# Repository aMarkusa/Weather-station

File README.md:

# BLE Weather Station

The BLE Weather Station is a project I started in late 2022 as a way to get practical experience with developing low-power IoT solutions.

## Working principle
The weather station consists of two main components: a central device serving as the station, and a peripheral device serving as a temperature node.

### Peripheral device
   
The peripheral device consists of a Renesas DA14531 BLE module together with a STS40 temperature sensor. The peripheral device performs a temperature reading every 10min, and includes this reading in its advertisement data. The BLE module is set to advertise with an interval of 1s.  
The peripheral is powered with a CR2450 cell-battery. In order to minimize current consumption, non-connectable advertisements are used together with extended sleep which is entered between advertisement. With this configuration, estimations done with a power analyzer results in a battery life of ~4 years. 

### Central device
   
The main components of the central device is a Renesas DA14531 BLE module, BME680 environmental sensor, and a 4.2" E-Paper display. The central device spends most of its time in deep sleep, but wakes up every 30min to performs its task. After waking up, the central device starts scanning for the peripheral device. If the peripheral device is detected, the central reads the peripherals temperature from the advertisement data. If the peripheral cant be detected within 15s, the temperature value is set to 255. After the peripheral temperature is set, the central device performs a reading from the BME680 sensor (temperature, humidity, air-pressure, gas-resistance). So, at this point, the central has acquired 5 data values:

&nbsp;&nbsp;&nbsp;&nbsp;1. Peripheral temperature  
&nbsp;&nbsp;&nbsp;&nbsp;2. Central temperature  
&nbsp;&nbsp;&nbsp;&nbsp;3. Central humidity  
&nbsp;&nbsp;&nbsp;&nbsp;4. Central air-pressure  
&nbsp;&nbsp;&nbsp;&nbsp;5. Central gas resistance 

These values are then displayed on the E-Paper display, after which the central goes back to sleep.

## Current status
The project has reached the point where it is functioning as intended, but still has some unfinished tasks:

* Designing and 3D-printing enclosures for both the peripheral and the central.
* Calibrating the BME680's gas resistance reading and converting it into an air quality grade.
* Performing current consumption measurements on the central.

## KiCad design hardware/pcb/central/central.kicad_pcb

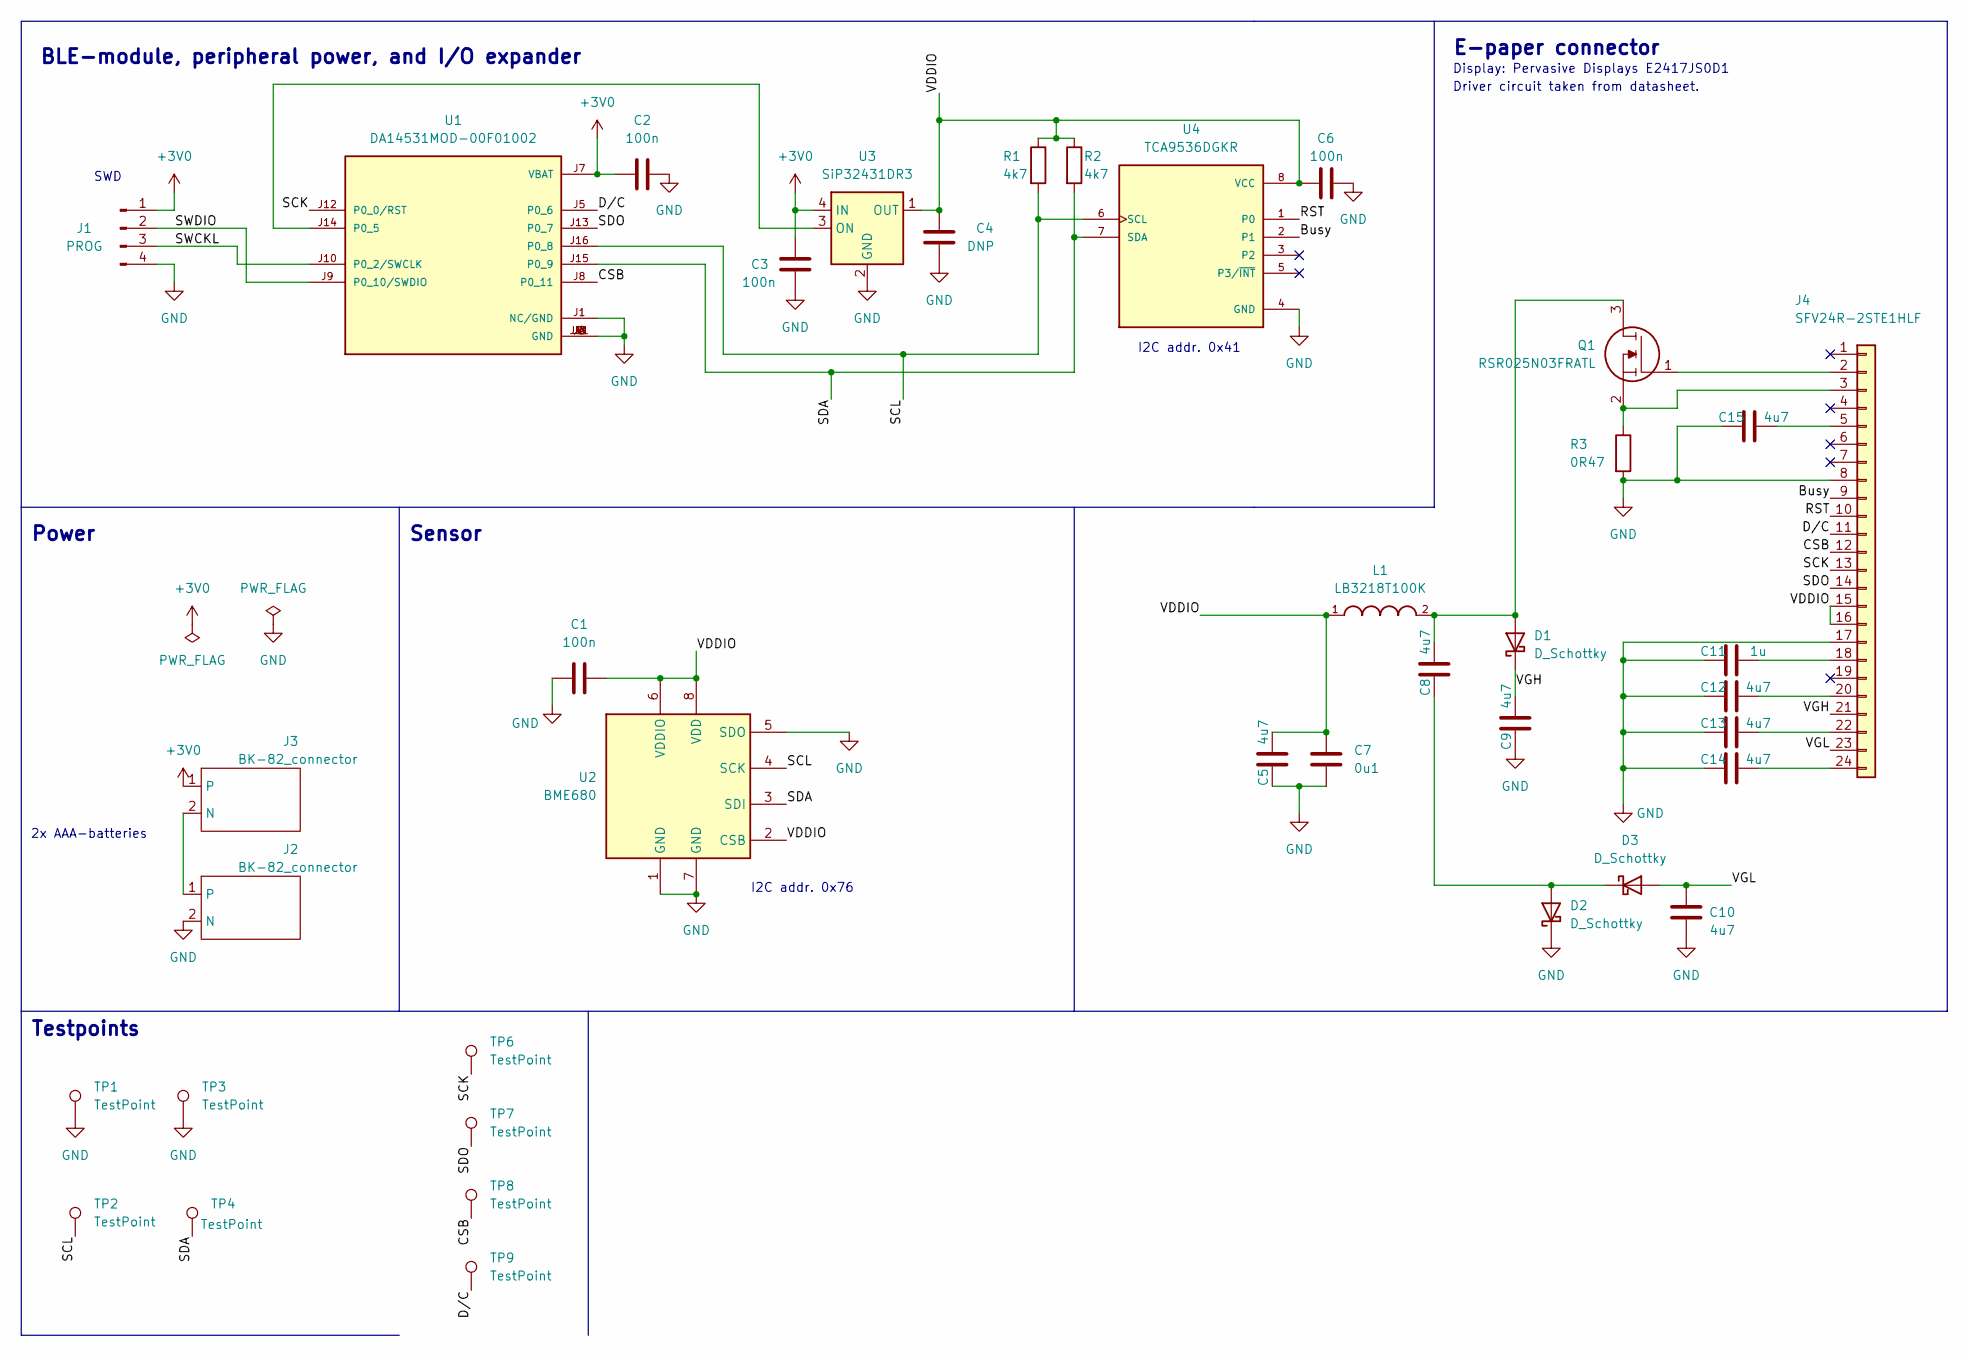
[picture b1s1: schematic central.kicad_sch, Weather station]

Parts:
C1, C2, C3, C6: 100n; C_0603_1608Metric_Pad1.08x0.95mm_HandSolder
C4: DNP; C_0603_1608Metric_Pad1.08x0.95mm_HandSolder
C5, C8, C9, C10, C12, C13, C14, C15: 4u7; C_0603_1608Metric_Pad1.08x0.95mm_HandSolder
C7: 0u1; C_0603_1608Metric_Pad1.08x0.95mm_HandSolder
C11: 1u; C_0603_1608Metric_Pad1.08x0.95mm_HandSolder
D1, D2, D3: D_Schottky; D_SOD-123F
J1: PROG; PinHeader_1x04_P2.54mm_Vertical
J2, J3: BK-82_connector; AA_battery_holder
J4: SFV24R-2STE1HLF
L1: LB3218T100K; INDC3218X200N
Q1: RSR025N03FRATL; SOT95P280X100-3N; Manufacturer_Part_Number RSR025N03FRATL
R1, R2: 4k7; R_0603_1608Metric_Pad0.98x0.95mm_HandSolder
R3: 0R47; R_0603_1608Metric_Pad0.98x0.95mm_HandSolder
TP1, TP2, TP3, TP4, TP6, TP7, TP8, TP9: TestPoint; TestPoint_Pad_1.0x1.0mm
U1: DA14531MOD-00F01002; XCVR_DA14531MOD-00F01002; PARTREV 3.1
U2: BME680; Bosch_LGA-8_3x3mm_P0.8mm_ClockwisePinNumbering
U3: SiP32431DR3; SOT-363_SC-70-6
U4: TCA9536DGKR; SOP65P490X110-8N; PARTREV A

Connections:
+3V0: C2.1, C3.2, J1.1, J3.1, U1.J7 (VBAT), U3.4 (IN)
/Busy: J4.9, U4.2 (P1)
/CSB: J4.12, TP8.1, U1.J8 (P0_11)
/D/C: J4.11, TP9.1, U1.J5 (P0_6)
/RST: J4.10, U4.1 (P0)
/SCK: J4.13, TP6.1, U1.J12 (P0_0/RST)
/SCL: R1.2, TP2.1, U1.J16 (P0_8), U2.4 (SCK), U4.6 (SCL)
/SDA: R2.2, TP4.1, U1.J15 (P0_9), U2.3 (SDI), U4.7 (SDA)
/SDO: J4.14, TP7.1, U1.J13 (P0_7)
/SWCKL: J1.3, U1.J10 (P0_2/SWCLK)
/SWDIO: J1.2, U1.J9 (P0_10/SWDIO)
/VDDIO: C1.2, C4.2, C5.2, C6.2, C7.1, J4.15, J4.16, L1.1, R1.1, R2.1, U2.2 (CSB), U2.6 (VDDIO), U2.8 (VDD), U3.1 (OUT), U4.8 (VCC)
/VGH: C9.2, D1.1 (K), J4.21
/VGL: C10.2, D3.2 (A), J4.23
GND: C1.1, C2.2, C3.1, C4.1, C5.1, C6.1, C7.2, C9.1, C10.1, C11.1, C12.1, C13.1, C14.1, C15.1, D2.1 (K), J1.4, J2.2 (N), J4.8, J4.17, R3.2, TP1.1, TP3.1, U1.J1 (NC/GND), U1.J2 (GND), U1.J3 (GND), U1.J4 (GND), U1.J6 (GND), U1.J11 (GND), U2.1 (GND), U2.5 (SDO), U2.7 (GND), U3.2 (GND), U3.5 (GND), U4.4 (GND)
unnamed: C8.1, D2.2 (A), D3.1 (K)
unnamed: C8.2, D1.2 (A), L1.2, Q1.3
unnamed: C11.2, J4.18
unnamed: C12.2, J4.20
unnamed: C13.2, J4.22
unnamed: C14.2, J4.24
unnamed: C15.2, J4.5
unnamed: J2.1, J3.2 (N)
unnamed: J4.2, Q1.1
unnamed: J4.3, Q1.2, R3.1
unnamed: U1.J14 (P0_5), U3.3 (ON)

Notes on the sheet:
SWD
I2C addr. 0x41
Testpoints
I2C addr. 0x76
Driver circuit taken from datasheet.
Power
2x AAA-batteries
Sensor
E-paper connector
Display: Pervasive Displays E2417JS0D1
BLE-module, peripheral power, and I/O expander

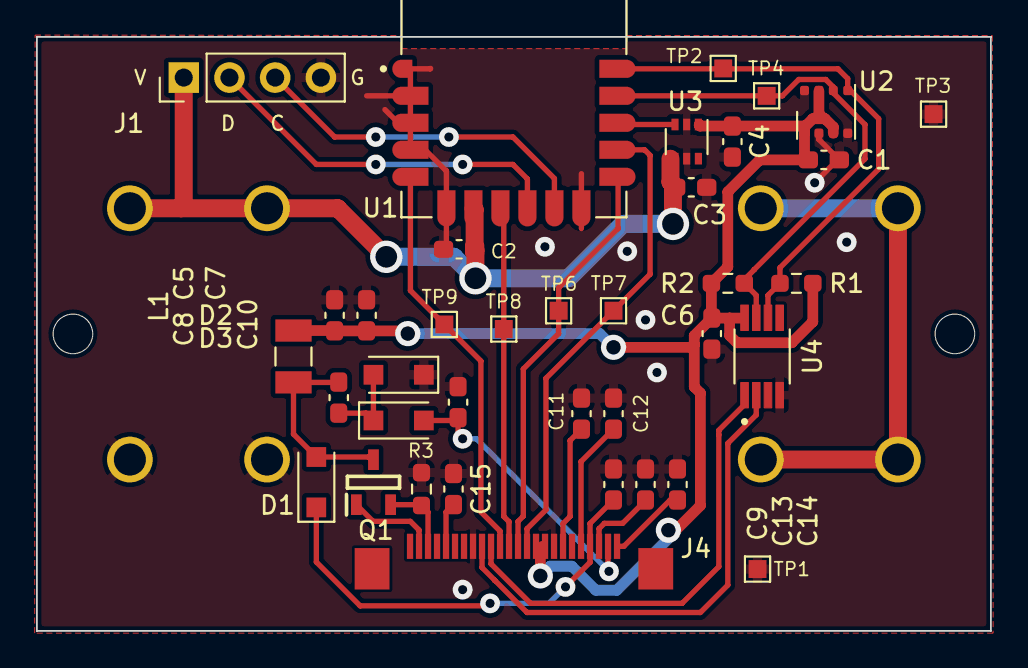
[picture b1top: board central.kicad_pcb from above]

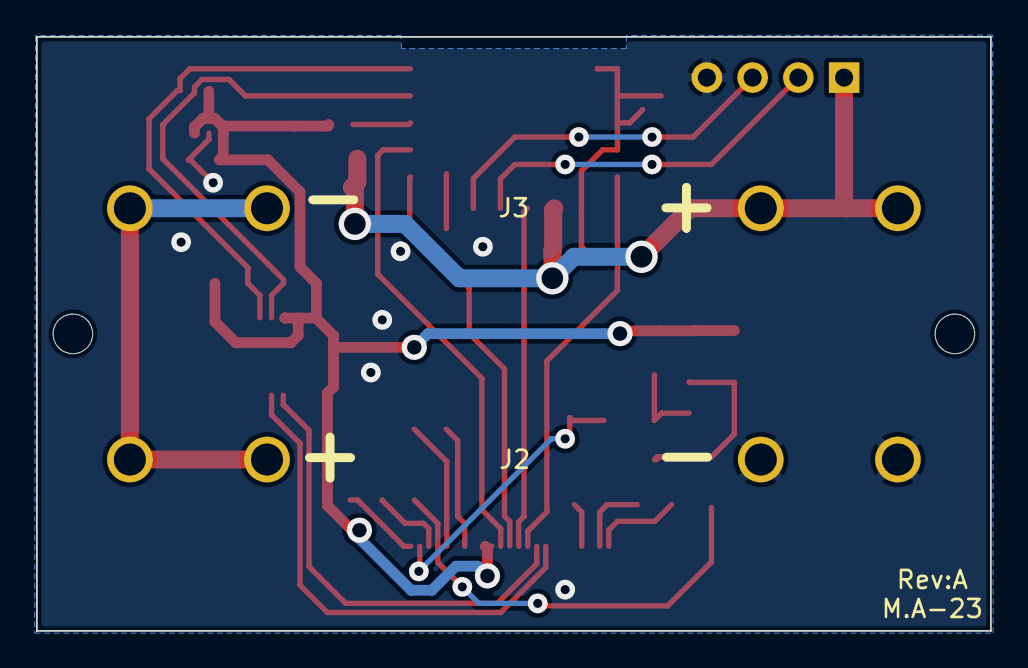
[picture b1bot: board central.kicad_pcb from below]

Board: 2 copper layers, 53.0 x 33.0 mm, 41 parts (2 on the bottom side), 26 nets.

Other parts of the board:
MH1, MH2: MountingHole_2.2mm_M2_DIN965

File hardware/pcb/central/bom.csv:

"Id","Designator","Package","Quantity","Designation","Supplier and ref"
1,"TP6,TP4,TP3,TP9,TP2,TP7,TP8,TP1","TestPoint_Pad_1.0x1.0mm",8,"TestPoint",
2,"U4","SOP65P490X110-8N",1,"TCA9536DGKR",
3,"C13,C14,C9,C8,C5,C12,C10,C15","C_0603_1608Metric_Pad1.08x0.95mm_HandSolder",8,"4u7",
4,"U2","Bosch_LGA-8_3x3mm_P0.8mm_ClockwisePinNumbering",1,"BME680",
5,"U1","XCVR_DA14531MOD-00F01002",1,"DA14531MOD-00F01002",
6,"C4","C_0603_1608Metric_Pad1.08x0.95mm_HandSolder",1,"DNP",
7,"Q1","SOT95P280X100-3N",1,"RSR025N03FRATL",
8,"U3","SOT-363_SC-70-6",1,"SiP32431DR3",
9,"C2,C6,C1,C3","C_0603_1608Metric_Pad1.08x0.95mm_HandSolder",4,"100n",
10,"J4","SFV24R-2STE1HLF",1,"SFV24R-2STE1HLF",
11,"R3","R_0603_1608Metric_Pad0.98x0.95mm_HandSolder",1,"0R47",
12,"R2,R1","R_0603_1608Metric_Pad0.98x0.95mm_HandSolder",2,"4k7",
13,"C7","C_0603_1608Metric_Pad1.08x0.95mm_HandSolder",1,"0u1",
14,"D1,D2,D3","D_SOD-123F",3,"D_Schottky",
15,"L1","INDC3218X200N",1,"LB3218T100K",
16,"J1","PinHeader_1x04_P2.54mm_Vertical",1,"PROG",
17,"C11","C_0603_1608Metric_Pad1.08x0.95mm_HandSolder",1,"1u",
18,"J2,J3","AAA_battery_holder",2,"BK-82_connector",

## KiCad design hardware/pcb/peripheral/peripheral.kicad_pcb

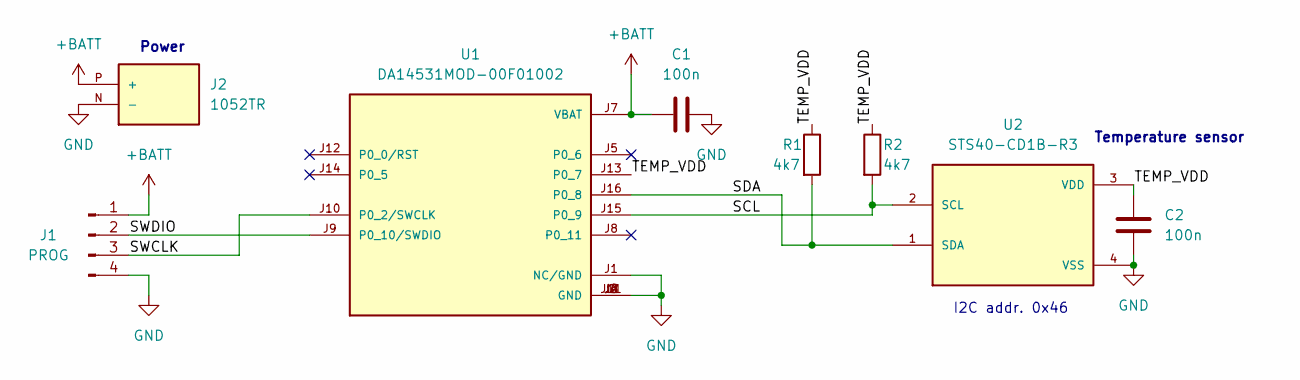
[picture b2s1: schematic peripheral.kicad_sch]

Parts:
C1, C2: 100n; C_0603_1608Metric_Pad1.08x0.95mm_HandSolder
J1: PROG; PinHeader_1x04_P2.54mm_Vertical
J2: 1052TR; KEYSTONE_1052TR; PARTREV B
R1, R2: 4k7; R_0603_1608Metric_Pad0.98x0.95mm_HandSolder
U1: DA14531MOD-00F01002; XCVR_DA14531MOD-00F01002; PARTREV 3.1
U2: STS40-CD1B-R3; STS4X

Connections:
+BATT: C1.1, J1.1, J2.P (+), U1.J7 (VBAT)
/SCL: R2.2, U1.J15 (P0_9), U2.2 (SCL)
/SDA: R1.2, U1.J16 (P0_8), U2.1 (SDA)
/SWCLK: J1.3, U1.J10 (P0_2/SWCLK)
/SWDIO: J1.2, U1.J9 (P0_10/SWDIO)
/TEMP_VDD: C2.2, R1.1, R2.1, U1.J13 (P0_7), U2.3 (VDD)
GND: C1.2, C2.1, J1.4, J2.N (-), U1.J1 (NC/GND), U1.J2 (GND), U1.J3 (GND), U1.J4 (GND), U1.J6 (GND), U1.J11 (GND), U2.4 (VSS)

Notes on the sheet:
Power
I2C addr. 0x46
Temperature sensor

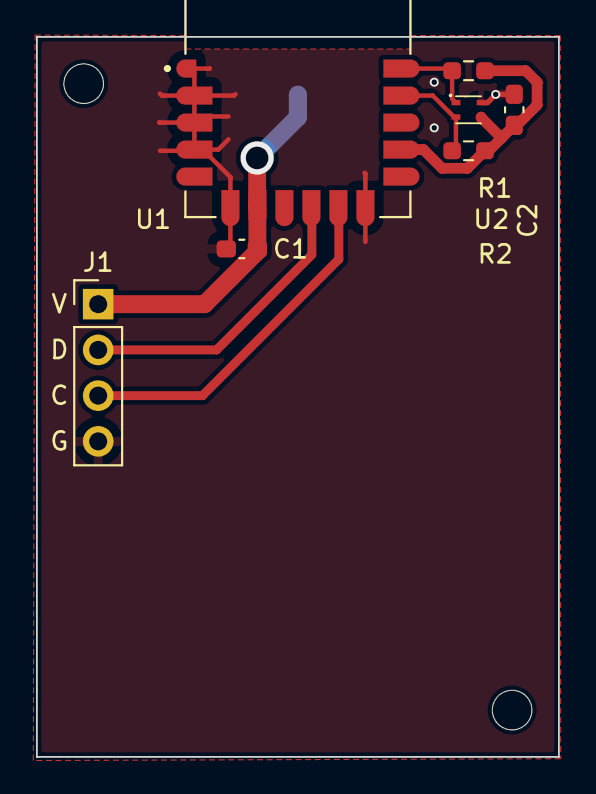
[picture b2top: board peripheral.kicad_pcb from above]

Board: 2 copper layers, 29.0 x 40.0 mm, 10 parts (1 on the bottom side), 7 nets.

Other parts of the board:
MH1, MH2: MountingHole_2.2mm_M2_DIN965

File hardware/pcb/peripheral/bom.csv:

"ID";"Beteckning";"Paket";"Kvantitet";"Beteckning";"Leverantör och ref";
1;"R1,R2";"R_0603_1608Metric_Pad0.98x0.95mm_HandSolder";2;"4k7";;;
2;"C1,C2";"C_0603_1608Metric_Pad1.08x0.95mm_HandSolder";2;"100n";;;
3;"U2";"STS4X";1;"STS40-CD1B-R3";;;
4;"U1";"XCVR_DA14531MOD-00F01002";1;"DA14531MOD-00F01002";;;
5;"J1";"PinHeader_1x04_P2.54mm_Vertical";1;"PROG";;;
6;"J2";"KEYSTONE_1052TR";1;"1052TR";;;

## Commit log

2023-04-01 added temp sensor
2023-04-19 corrected data
2023-04-29 power switch is working
2023-05-17 started porting BME680 lib
2023-05-19 integrated new bme680 library
2023-05-26 Added image
2023-05-26 added gitignore
2023-05-26 Removed display folder
2023-05-26 updated gitignore
2023-05-26 update gitignore
2023-05-26 renamed driver/ to bosch_driver/
2023-05-26 removed folders
2023-05-26 added pcb
2023-05-26 edited bom
2023-05-27 new driver for BME680
2023-05-27 bme680 now working
2023-06-10 added asset folder to .gitignore
2023-06-10 removed ignored folder
2023-06-10 added project_environment folder to .gitignore
2023-06-10 cleared readme
2023-06-11 Revert "added project_environment folder to .gitignore"
    This reverts commit 6cd4016c46cb7c664b78b5c9642d8492a3e10072.
2023-06-11 Revert "removed ignored folder"
    This reverts commit 5d18b70d45b3b148cdf50e64b88f2fb00754bb83.
2023-07-15 Revert "Revert "removed ignored folder""
    This reverts commit 5fe4d0102513803c8b2874ef812e2948254e80de.
2023-07-15 Revert "cleared readme"
    This reverts commit 3ee01627e0d87b44c5958172edd9aeb340014ca2.
2023-08-31 removed old project and replaced with new
2023-09-01 flipped the bytes so they show up correctly on display
2023-09-01 font size works
2023-09-01 improved logic of scale_byte
2023-09-01 added degree symbol and strings
2023-09-02 added BME680 related files'
2023-09-11 successfully integrated bme680
2023-09-12 improved formatting
2023-09-14 cleanup and commenting. Ready for merge
2023-09-16 added images folder
2023-09-16 removed unused folder
2023-09-16 resize image
2023-09-16 added display image
2023-09-16 image update
2023-09-20 changed example base
2023-09-20 finishing touches
2023-10-01 added deep sleep. Not yet verified
2023-10-11 deep sleep now working. Also added limit for scanning duration.
2023-10-19 added description of project
2023-10-19 new images
2023-10-19 updated image paths
2023-10-19 temporarily removed images
2023-10-20 edit image size
2023-10-20 added new images
2023-10-20 new image of whole station
2023-10-20 edit image path
